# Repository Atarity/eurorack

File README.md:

# Eurorack DIY projects
- 4x4 — eurorack compatible breadboard with adjustable width
- Pike — 4HP power for small racks (Befaco Excalibus relayout)

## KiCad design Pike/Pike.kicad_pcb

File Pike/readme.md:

# Pike
Pike — 4HP power for compact racks. It based on turn-key MeanWell PSU with minimum possible additional components. Pike is just a relayout of [Excalibus power bus by Befaco](https://www.befaco.org/excalibus/) made to use with flying bus.

- [Mouser cart](https://www.mouser.fi/ProjectManager/ProjectDetail.aspx?AccessID=896566e5e1)
- [Blog post with project details](https://snnkv.com/projects/pike/)

## Specs
- IN
    - DC 9-18V
    - You can use 15V@3A (45W) external AC-DC power supply from laptop
    - Central pin positive (socket pin 2.1mm)
- OUT
    - +12V up to 1.25A
    - -12V up to 1.25A
    - +5V up to 0.4A

## Dimensions
- Height: 3U
- Width: 4HP
- Depth: 28mm

It is possible to install module inside of a rack thru M2-M2.5 screws and not to use front panel at all.

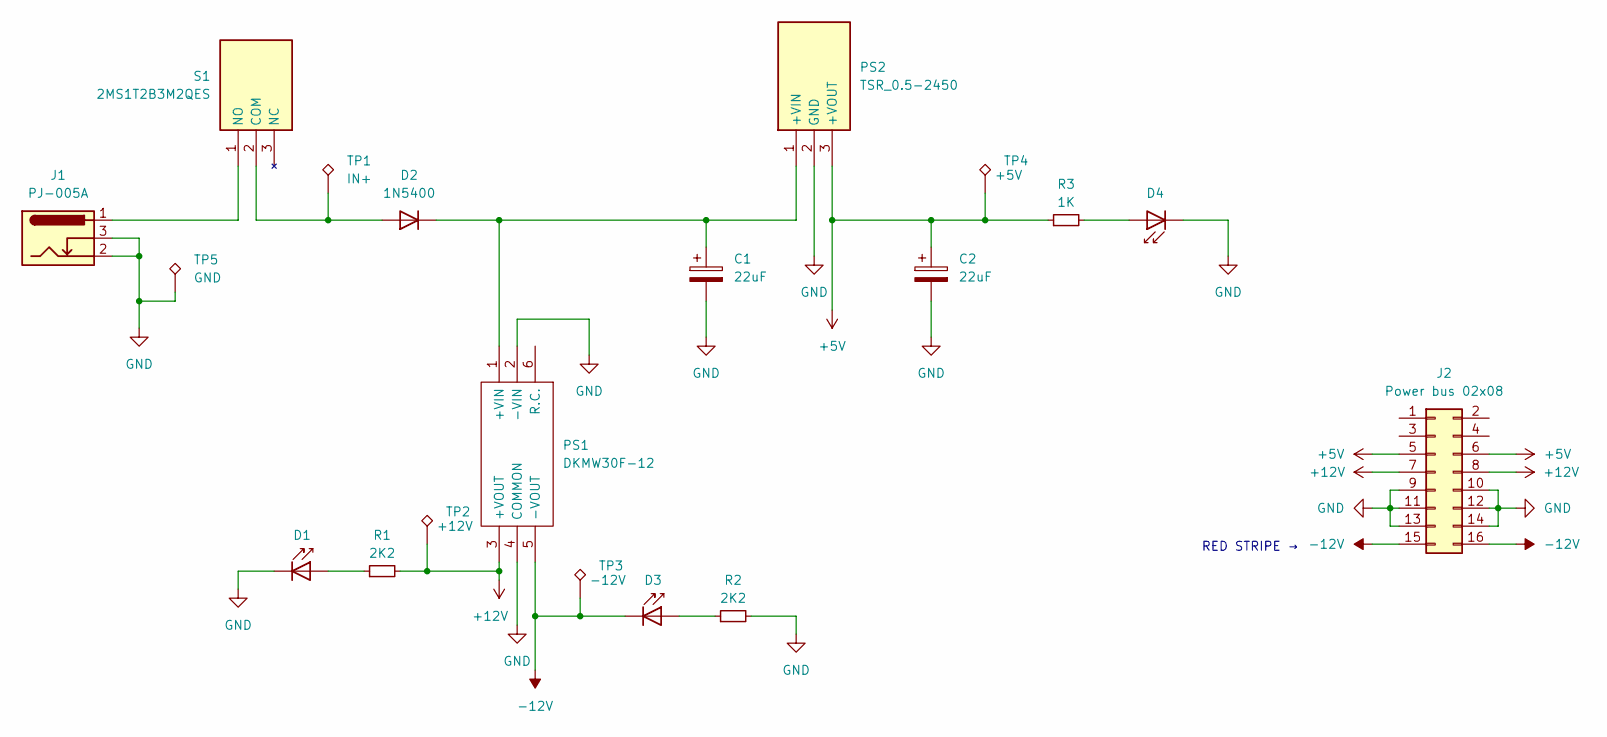
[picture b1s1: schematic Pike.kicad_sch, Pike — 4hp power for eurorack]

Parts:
C1, C2: 22uF; CP_Radial_D6.3mm_P2.50mm; Mouser Part Number 667-ECE-A1HKA220
D1, D3, D4: 604-WP424GDT; LED_D3.0mm_IRBlack; Mouser Part Number 604-WP424GDT
D2: 1N5400; D_DO-201AD_P15.24mm_Horizontal; Mouser Part Number 863-1N5400G
J1: PJ-005A; PJ005A; Mouser Part Number 490-PJ-005A
J2: Power bus 02x08; PinHeader_2x08_P2.54mm_Vertical
PS1: DKMW30F-12; DKMW30F15; Mouser Part Number 709-DKMW30F-12
PS2: TSR_0.5-2450; TSR-0.5-2433; Mouser Part Number 495-TSR0.5-2450
R1, R2: 2K2; R_Axial_DIN0207_L6.3mm_D2.5mm_P7.62mm_Horizontal; Mouser Part Number CFR25SJT-26-2K2
R3: 1K; R_Axial_DIN0207_L6.3mm_D2.5mm_P7.62mm_Horizontal; Mouser Part Number CFR-25JB-1K0
S1: 2MS1T2B3M2QES; 2MS1-pcb-edge; Mouser Part Number 118-2MS1T2B3M2QES
TP1: IN+; TestPoint_Pad_D1.0mm
TP2: +12V; TestPoint_Pad_D1.0mm
TP3: -12V; TestPoint_Pad_D1.0mm
TP4: +5V; TestPoint_Pad_D1.0mm
TP5: GND; TestPoint_Pad_D1.0mm

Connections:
+5V: C2.1, J2.5, J2.6, PS2.3 (+VOUT), R3.1, TP4.1
+12V: J2.7, J2.8, PS1.3 (+VOUT), R1.2, TP2.1
-12V: D3.1 (K), J2.15, J2.16, PS1.5 (-VOUT), TP3.1
GND: C1.2, C2.2, D1.1 (K), D4.1 (K), J1.2, J1.3, J2.9, J2.10, J2.11, J2.12, J2.13, J2.14, PS1.2 (-VIN), PS1.4 (COMMON), PS2.2 (GND), R2.2, TP5.1
unnamed: D1.2 (A), R1.1
unnamed: D2.2 (A), S1.2 (COM), TP1.1
unnamed: C1.1, D2.1 (K), PS1.1 (+VIN), PS2.1 (+VIN)
unnamed: D3.2 (A), R2.1
unnamed: D4.2 (A), R3.2
unnamed: J1.1, S1.1 (NO)

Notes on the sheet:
RED STRIPE →

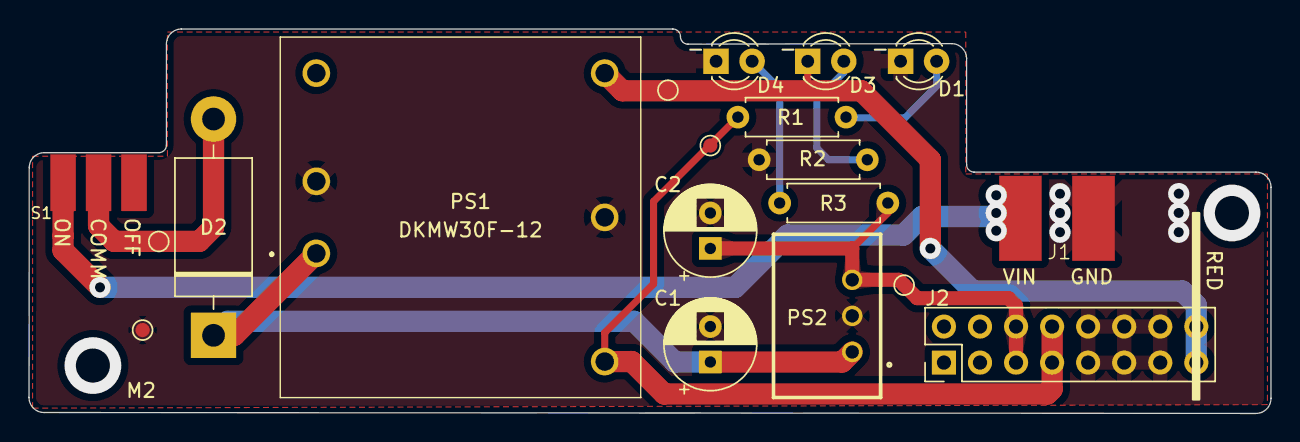
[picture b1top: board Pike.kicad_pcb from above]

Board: 2 copper layers, 87.5 x 27.1 mm, 19 parts (0 on the bottom side), 10 nets.

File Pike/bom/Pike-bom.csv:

“#”,”Reference”,”Value”,”Qty”,”Description”,”Mouser Part Number”
“1”,”C1,C2”,”22uF”,”2”,”Aluminium Electrolytic Capacitors - Radial Leaded, Panasonic”,”667-ECE-A1HKA220”
“2”,”D2”,”1N5400”,”1”,”Rectifiers 50V 3A Standard”,”863-1N5400G”
“3”,”D1,D3,D4”,”604-WP424GDT”,”3”,”Single Colour LEDs 3MM FLAT TOP GRN”,”604-WP424GDT”
“4”,”J1”,”PJ-005A”,”1”,”DC Power Connectors Power Jack”,”490-PJ-005A”
“5”,”PS1”,”DKMW30F-12”,”1”,”Isolated DC/DC Converters 9-36Vin +/-12Vout +/-1250mA DIP Iso”,”709-DKMW30F-12”
“6”,”PS2”,”TSR_0.5-2450”,”1”,”Non-Isolated DC/DC Converter (TRACO)”,”495-TSR0.5-2450”
“7”,”R3”,”1K”,”1”,”Through Hole 1K 250 mW 5 %”,”CFR-25JB-1K0”
“8”,”R1,R2”,”2K2”,”2”,”Through Hole 2K2 250 mW 5 %”,”CFR25SJT-26-2K2”
“9”,”S1”,”2MS1T2B3M2QES”,”1”,”Toggle Switches SPDT ON-ON PC MOUNT”,”118-2MS1T2B3M2QES”
“10”,”J2”,”Power bus 02x08”,”1”,”2.54 pitch pin reel 2x8”,””

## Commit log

2025-01-22 initial
2025-01-24 all gathered
2025-01-24 typos
2025-01-24 links
2025-01-24 pics order
